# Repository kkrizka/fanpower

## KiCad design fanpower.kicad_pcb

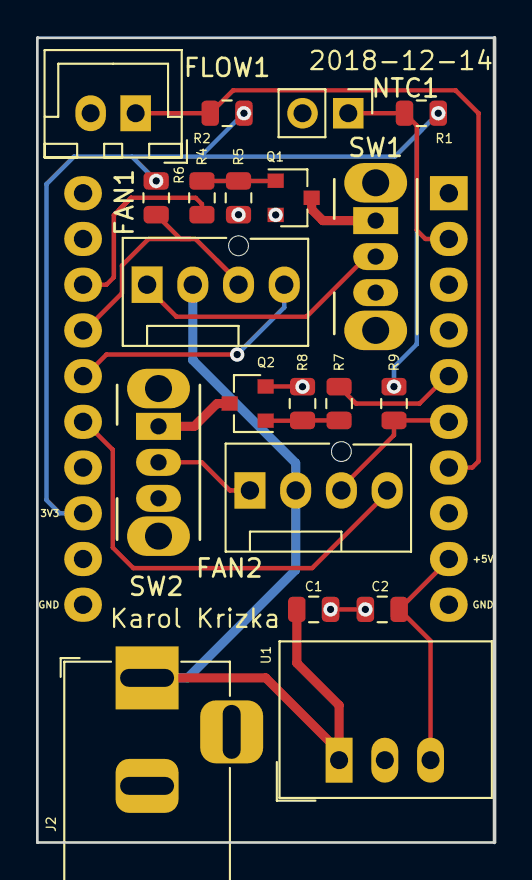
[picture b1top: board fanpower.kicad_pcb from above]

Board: 2 copper layers, 25.4 x 44.7 mm, 21 parts (1 on the bottom side), 18 nets.

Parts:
A1: Adafruit_HUZZAH_ESP8266_breakout
C1, C2: 10uF; C_0805_2012Metric
FAN1, FAN2: Conn_01x04; FanPinHeader_1x04_P2.54mm_Vertical
FLOW1: Conn_01x02; JST_XH_B02B-XH-A_1x02_P2.50mm_Vertical
J2: Conn_01x03; BarrelJack_Horizontal
NTC1: Conn_01x02; PinHeader_1x02_P2.54mm_Vertical
Q1, Q2: BSH105,215; SOT-23
R1, R2, R5, R6, R8, R9: 10k; R_0805_2012Metric
R4, R7: 100; R_0805_2012Metric
SW1, SW2: SW_SPDT; SW_CuK_OS102011MA1QN1_SPDT_Angled
U1: R-78E5.0-0.5; Converter_DCDC_RECOM_R-78E-0.5_THT

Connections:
+3V3: A1.13, R1.1, R2.1, R6.1, R9.1
+5V: A1.9, C2.1, U1.3
+12V: C1.1, FAN1.2, FAN2.2, J2.1, U1.1
/FLOW: A1.7, FLOW1.1, R2.2
/NTC: A1.2, NTC1.1, R1.2
/SIGON1: A1.18, R4.2
/SIGON2: A1.5, R7.2
/SIGPWM1: A1.16, FAN1.4
/SIGPWM2: A1.15, FAN2.4
/SIGTACH1: A1.17, FAN1.3, R6.2
/SIGTACH2: A1.6, FAN2.3, R9.2
GND: A1.10, A1.11, C1.2, C2.2, FLOW1.2, J2.2, NTC1.2, Q1.2, Q2.2, R5.2, R8.2, SW1.3, SW2.3, U1.2
unnamed: FAN1.1, SW1.2
unnamed: FAN2.1, SW2.2
unnamed: Q1.1, R4.1, R5.1
unnamed: Q1.3, SW1.1
unnamed: Q2.1, R7.1, R8.1
unnamed: Q2.3, SW2.1

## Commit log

2018-11-26 Initial import.
2018-11-26 pumppower -> fanpower
2018-11-26 Add schematic PDF.
2018-11-27 Preliminary layout.
2018-11-27 Add FLOW measurement.
2018-11-27 Change connector for FLOW connector.
2018-11-27 Make board a bit longer.
2018-11-28 Use keyed connector for flow measurement.
2018-12-14 Update.
2018-12-15 Fix fan pinout. The +12V and GND were swapped.
